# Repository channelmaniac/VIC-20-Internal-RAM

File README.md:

# VIC-20-Internal-RAM
An internal RAM expansion board for the VIC-20.

The VIC-20 is an interesting computer, but has an oddity in that you're limited to one cartridge at a time... Do you use memory? Do you use some other hardware interface? I thought it was a bit silly so I created an internal memory upgrade board. I also did this as a learning experience as this is my first GAL to design the equations for. 

This board uses a single 32K x 8 SRAM chip and a bank of 6 DIP switches to enable/disable individual banks of memory using the already decoded memory bank enables on the cartridge port:

These represent the 3K expansion cartridge:
* RAM 1 = 0400 - 07FF
* RAM 2 = 0800 - 0BFF
* RAM 3 = 0C00 - 0FFF

These represent the 8, 16, and 24K cartridges:
* Block 1 = 2000 - 3FFF
* Block 2 = 4000 - 5FFF
* Block 3 = 6000 = 7FFF

The board uses a few flying wires for the signals it cannot get from the CPU which include the above mention memory bank enables from the cartridge port plus the VR/W signal off the same cartridge port.

The only shortcoming with this board is that the DIPs are internal. This can cause problems with some game cartridges, notably the ones that use Block 1, 2, and/or 3 instead of Block 5 (A000 - BFFF) for the ROM addresses. Star Trek Strategic Operations Simulator is one such cartridge that uses Block 1 address space.

The PCB is easy to build, with only one surface mount part - the SOJ packaged static RAM chip. As for the GAL, any 16V8x should work for it. I used a GAL16V8A-25 in my initial build. GALs are reusable, so no need to go buy one if you have a scrap PCB you can salvage one from. I pulled the one I used off an old 8-liner gambling PCB that I already pulled the ROMs, SRAMs, and Z80 off of for use in repairing arcade game PCBs. You can use a right angle header for the flying wires or solder wires straight to the PCB, that's up to you, but for clearance, don't use a straight header or you'll hit the keyboard above the PCB. **The pins on the header connecting to the CPU socket must be trimmed to not interfere with the placement of the CPU socket on the PCB. Also, the pins on the DIP switches, GAL, and input header need to be trimmed to clear the ROM next to the CPU.** While it's not critical to clear the ROM if you have sufficient contact with the CPU socket, It personally bugs me to see a PCB touching chips under it and not seating down level in the socket.

It has been tested in the revision of VIC-20 that runs off a DC supply. It should fit in the older revision, but has not been tested in one as of yet.

Inputs are labeled on the bottom silk screen. DIP switch info is on the top silk screen.

The cartridge pins for connections are easy to access and are on the upper set so no need to try to get to the bottom row for attaching the wires.

Cartridge slot pin: Signal Name
* 10 - Block 1
* 11 - Block 2
* 12 - Block 3
* 13 - Block 5 (NOT USED)
* 14 - RAM 1
* 15 - RAM 2
* 16 - RAM 3
* 17 - VR/W

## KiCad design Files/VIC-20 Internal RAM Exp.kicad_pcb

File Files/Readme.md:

# VIC-20-Internal-RAM

Here are the KiCAD files. Feel free to play with them and modify them for your usage, but please give me credit for the initial design.

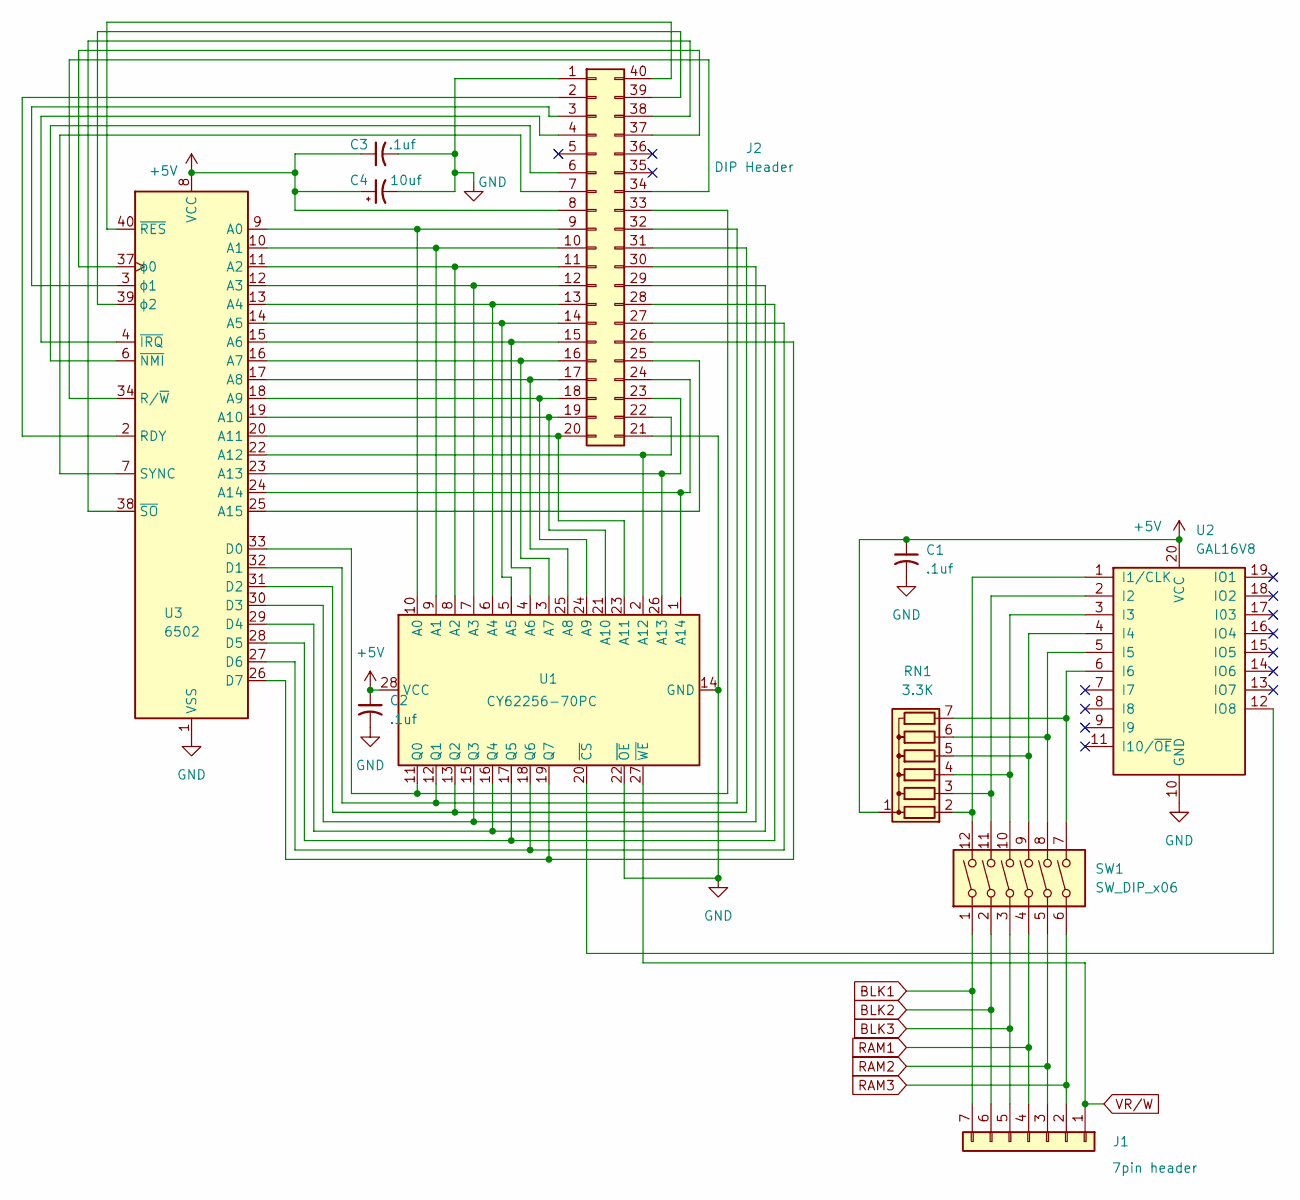
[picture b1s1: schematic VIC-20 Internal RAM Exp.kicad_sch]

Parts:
C1, C2, C3: .1uf; C_Disc_D3.0mm_W2.0mm_P2.50mm
C4: 10uf; CP_Radial_D5.0mm_P2.50mm
J1: 7pin header; PinHeader_1x07_P2.54mm_Horizontal
J2: DIP Header; DIP-40_W15.24mm
RN1: 3.3K; R_Array_SIP7
SW1: SW_DIP_x06; SW_DIP_SPSTx06_Slide_9.78x17.42mm_W7.62mm_P2.54mm
U1: CY62256-70PC; SOIC-28W_7.5x17.9mm_P1.27mm
U2: GAL16V8; DIP-20_W7.62mm
U3: 6502; DIP-40_W15.24mm

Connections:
+5V: C1.1, C2.1, C3.1, C4.1, J2.8, RN1.1 (common), U1.28 (VCC), U2.20 (VCC), U3.8 (VCC)
BLK1: J1.7, SW1.1
BLK2: J1.6, SW1.2
BLK3: J1.5, SW1.3
GND: C1.2, C2.2, C3.2, C4.2, J2.1, J2.21, U1.14 (GND), U1.22 (~OE), U2.10 (GND), U3.1 (VSS), U3.21 (VSS)
unnamed: J2.2, U3.2 (RDY)
unnamed: J2.3, U3.3 (ϕ1)
unnamed: J2.4, U3.4 (~IRQ)
unnamed: J2.6, U3.6 (~NMI)
unnamed: J2.7, U3.7 (SYNC)
unnamed: J2.9, U1.10 (A0), U3.9 (A0)
unnamed: J2.10, U1.9 (A1), U3.10 (A1)
unnamed: J2.11, U1.8 (A2), U3.11 (A2)
unnamed: J2.12, U1.7 (A3), U3.12 (A3)
unnamed: J2.13, U1.6 (A4), U3.13 (A4)
unnamed: J2.14, U1.5 (A5), U3.14 (A5)
unnamed: J2.15, U1.4 (A6), U3.15 (A6)
unnamed: J2.16, U1.3 (A7), U3.16 (A7)
unnamed: J2.17, U1.25 (A8), U3.17 (A8)
unnamed: J2.18, U1.24 (A9), U3.18 (A9)
unnamed: J2.19, U1.21 (A10), U3.19 (A10)
unnamed: J2.20, U1.23 (A11), U3.20 (A11)
unnamed: J2.22, U1.2 (A12), U3.22 (A12)
unnamed: J2.23, U1.26 (A13), U3.23 (A13)
unnamed: J2.24, U1.1 (A14), U3.24 (A14)
unnamed: J2.25, U3.25 (A15)
unnamed: J2.26, U1.19 (Q7), U3.26 (D7)
unnamed: J2.27, U1.18 (Q6), U3.27 (D6)
unnamed: J2.28, U1.17 (Q5), U3.28 (D5)
unnamed: J2.29, U1.16 (Q4), U3.29 (D4)
unnamed: J2.30, U1.15 (Q3), U3.30 (D3)
unnamed: J2.31, U1.13 (Q2), U3.31 (D2)
unnamed: J2.32, U1.12 (Q1), U3.32 (D1)
unnamed: J2.33, U1.11 (Q0), U3.33 (D0)
unnamed: J2.34, U3.34 (R/~W)
unnamed: J2.37, U3.37 (ϕ0)
unnamed: J2.38, U3.38 (~SO)
unnamed: J2.39, U3.39 (ϕ2)
unnamed: J2.40, U3.40 (~RES)
unnamed: RN1.2 (R1), SW1.12, U2.1 (I1/CLK)
unnamed: RN1.3 (R2), SW1.11, U2.2 (I2)
unnamed: RN1.4 (R3), SW1.10, U2.3 (I3)
unnamed: RN1.5 (R4), SW1.9, U2.4 (I4)
unnamed: RN1.6 (R5), SW1.8, U2.5 (I5)
unnamed: RN1.7 (R6), SW1.7, U2.6 (I6)
unnamed: U1.20 (~CS), U2.12 (IO8)
RAM1: J1.4, SW1.4
RAM2: J1.3, SW1.5
RAM3: J1.2, SW1.6
VR/W: J1.1, U1.27 (~WE)

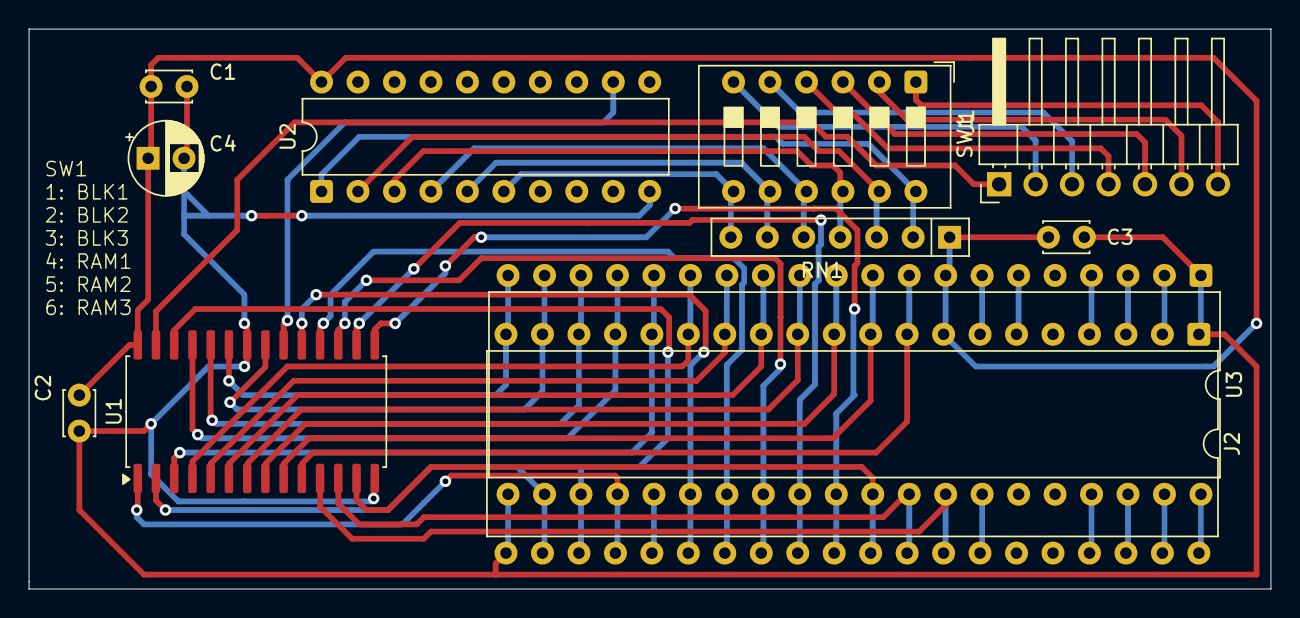
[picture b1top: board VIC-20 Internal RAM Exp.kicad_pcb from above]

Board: 2 copper layers, 86.5 x 39.0 mm, 11 parts (0 on the bottom side), 50 nets.

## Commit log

2025-07-14 Update README.md
    Inital posting of the file
2025-07-14 Add files via upload
    Add pics
2025-07-14 Update README.md
    Fix formatting
2025-07-14 Update README.md
    Add pics
2025-07-14 Create Readme.md
    Created file
2025-07-14 Add files via upload
    Added Gerbers
2025-07-14 Add files via upload
    Add BoM
2025-07-14 Update Readme.md
    Add sim pic
2025-07-15 Update README.md
    2 minor corrections
